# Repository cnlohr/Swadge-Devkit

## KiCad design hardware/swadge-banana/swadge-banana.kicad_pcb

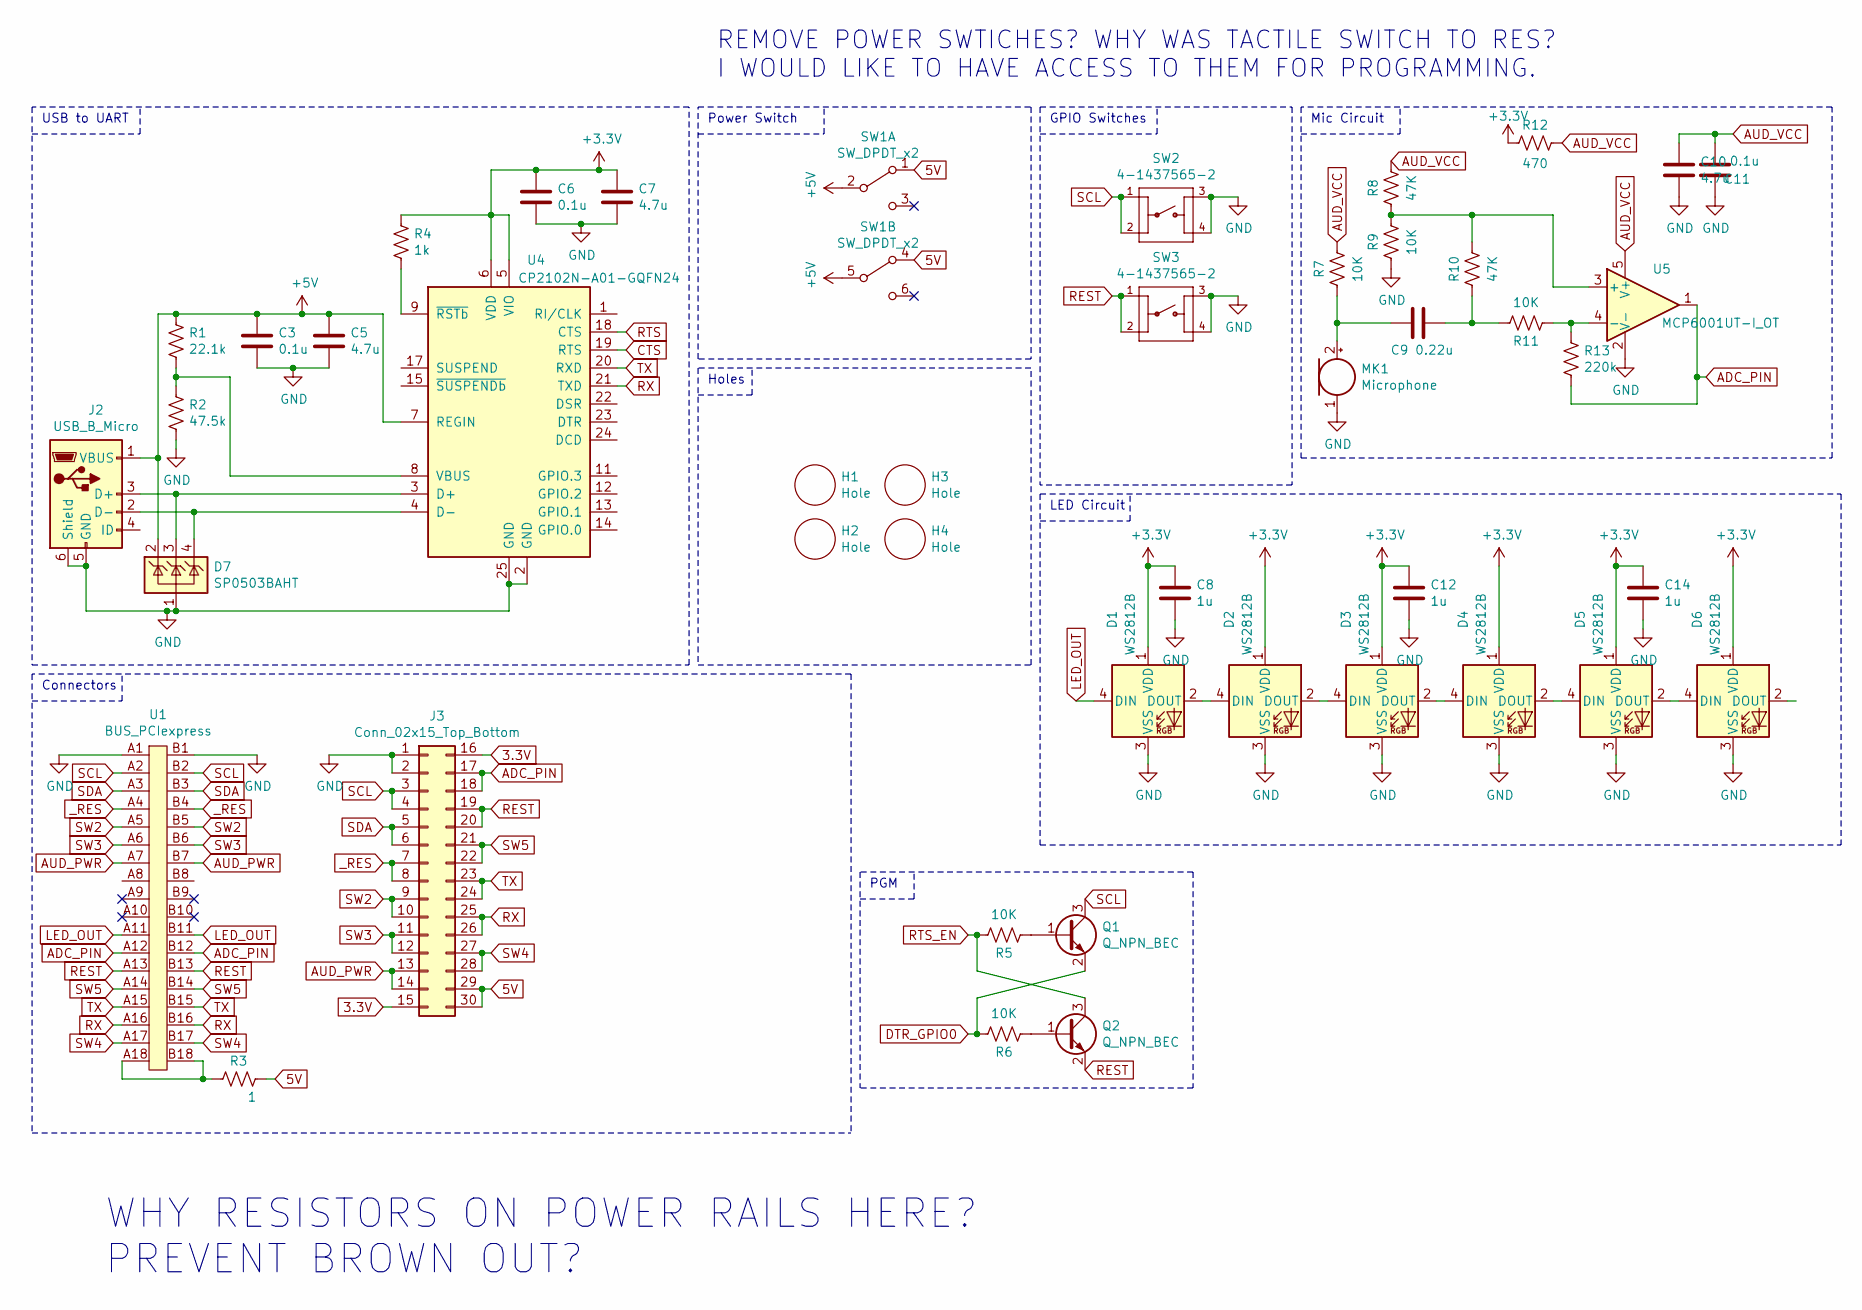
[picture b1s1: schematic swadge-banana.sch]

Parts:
C3, C6, C11: 0.1u; C_0603_1608Metric; Digikey 1276-1000-1-ND
C5, C7, C10: 4.7u; C_0603_1608Metric; Digikey 1276-1045-1-ND
C8, C12, C14: 1u; C_0603_1608Metric; Digikey 1276-1036-1-ND
C9: 0.22u; C_0603_1608Metric; Digikey 1276-2014-1-ND
D1, D2, D3, D4, D5, D6: WS2812B; LED_WS2812B_PLCC4_5.0x5.0mm_P3.2mm; Digikey 1528-1104-ND
D7: SP0503BAHT; SOT-143; Digikey F2715CT-ND
H1, H2, H3, H4: Hole; Digikey 2042-1007-ND
J2: USB_B_Micro; USB_Micro-B_Molex_47346-0001; Digikey WM17141CT-ND
J3: Conn_02x15_Top_Bottom; PinHeader_2x15_P2.54mm_Vertical; Digikey S2012EC-15-ND
MK1: Microphone; CMA-4544PF-W; Digikey 102-1721-ND
Q1, Q2: Q_NPN_BEC; SOT-23; Digikey BC848BLT3GOSTR-ND
R1: 22.1k; R_0603_1608Metric; Digikey RMCF0603FT22K1CT-ND
R2: 47.5k; R_0603_1608Metric; Digikey P47.5KHCT-ND
R3: 1; R_Axial_DIN0207_L6.3mm_D2.5mm_P10.16mm_Horizontal; Digikey RNF14FTD1R00CT-ND
R4: 1k; R_0603_1608Metric; Digikey 311-1.00KHRCT-ND
R5, R6, R7, R9, R11: 10K; R_0603_1608Metric; Digikey RNCP0603FTD10K0CT-ND
R8: 47K; R_0603_1608Metric; Digikey 311-470HRCT-ND
R10: 47K; R_0603_1608Metric; Digikey 311-47.0KHRCT-ND
R12: 470; R_0603_1608Metric; Digikey 311-470HRCT-ND
R13: 220k; R_0603_1608Metric; Digikey 311-220KHRCT-ND
SW1: SW_DPDT_x2; JS202011CQN; Digikey 401-2001-ND
SW2, SW3: 4-1437565-2; SW_4-1437565-2; MPN FSM4JSMATR; Digikey 450-1759-1-ND
U1: BUS_PCIexpress; 10018784-10210TLF; Digikey 609-2029-ND
U4: CP2102N-A01-GQFN24; QFN-24-1EP_4x4mm_P0.5mm_EP2.6x2.6mm; Digikey 336-4737-1-ND
U5: MCP6001UT-I_OT; SOT-23-5; Digikey MCP6001UT-I/OTCT-ND

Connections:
3.3V: J3.15, J3.16
5V: J3.29, J3.30, R3.2, SW1.1 (A), SW1.4 (A)
+3V3: C6.1, C7.1, C8.1, C12.1, C14.1, D1.1 (VDD), D2.1 (VDD), D3.1 (VDD), D4.1 (VDD), D5.1 (VDD), D6.1 (VDD), R4.2, R12.1, U4.5 (VIO), U4.6 (VDD)
ADC_PIN: J3.17, J3.18, R13.2, U1.A12, U1.B12, U5.1
AUD_PWR: J3.13, J3.14, U1.A7, U1.B7
AUD_VCC: C10.1, C11.2, R7.2, R8.2, R12.2, U5.5 (V+)
CTS: U4.19 (RTS)
DTR_GPIO0: Q1.2 (E), R6.2
GND: C3.2, C5.2, C6.2, C7.2, C8.2, C10.2, C11.1, C12.2, C14.2, D1.3 (VSS), D2.3 (VSS), D3.3 (VSS), D4.3 (VSS), D5.3 (VSS), D6.3 (VSS), D7.1 (A), J2.5 (GND), J2.6 (Shield), J3.1, J3.2, MK1.1 (-), R2.2, R9.1, SW2.3, SW2.4, SW3.3, SW3.4, U1.A1, U1.B1, U4.2 (GND), U4.25 (GND), U5.2 (V-)
LED_OUT: D1.4 (DIN), U1.A11, U1.B11
unnamed: C9.1, MK1.2 (+), R7.1
unnamed: C9.2, R10.1, R11.2
unnamed: D1.2 (DOUT), D2.4 (DIN)
unnamed: D2.2 (DOUT), D3.4 (DIN)
unnamed: D3.2 (DOUT), D4.4 (DIN)
unnamed: D4.2 (DOUT), D5.4 (DIN)
unnamed: D5.2 (DOUT), D6.4 (DIN)
unnamed: D7.3 (K), J2.3 (D+), U4.3 (D+)
unnamed: D7.4 (K), J2.2 (D-), U4.4 (D-)
unnamed: Q1.1 (B), R5.1
unnamed: Q2.1 (B), R6.1
unnamed: R1.2, R2.1, U4.8 (VBUS)
unnamed: R3.1, U1.A18, U1.B18
unnamed: R4.1, U4.9 (~RSTb)
unnamed: R8.1, R9.2, R10.2, U5.3 (+)
unnamed: R11.1, R13.1, U5.4 (-)
REST: J3.19, J3.20, Q2.2 (E), SW3.1, SW3.2, U1.A13, U1.B13
RTS: U4.18 (CTS)
RTS_EN: Q2.3 (C), R5.2
RX: J3.25, J3.26, U1.A16, U1.B16, U4.21 (TXD)
SCL: J3.3, J3.4, Q1.3 (C), SW2.1, SW2.2, U1.A2, U1.B2
SDA: J3.5, J3.6, U1.A3, U1.B3
SW2: J3.9, J3.10, U1.A5, U1.B5
SW3: J3.11, J3.12, U1.A6, U1.B6
SW4: J3.27, J3.28, U1.A17, U1.B17
SW5: J3.21, J3.22, U1.A14, U1.B14
TX: J3.23, J3.24, U1.A15, U1.B15, U4.20 (RXD)
_RES: J3.7, J3.8, U1.A4, U1.B4

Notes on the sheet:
LED Circuit
Power Switch
USB to UART
Connectors
Holes
Mic Circuit
GPIO Switches
REMOVE POWER SWTICHES? WHY WAS TACTILE SWITCH TO RES? I WOULD LIKE TO HAVE ACCESS TO THEM FOR PROGRAMMING.
WHY RESISTORS ON POWER RAILS HERE? PREVENT BROWN OUT?
PGM

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
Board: 2 copper layers, 45 parts (0 on the bottom side), 38 nets, no tracks yet.

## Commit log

2019-10-18 Update with my notional idea of what the banana swadge could be.
2019-10-21 Add my notional banana
